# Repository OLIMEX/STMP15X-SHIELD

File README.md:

# STMP15X-SHIELD
Shield for Industrial grade Linux Computer STMP157-OLinuXino which adds two UEXT, 40 GPIO, micro SD card

Product page: https://www.olimex.com/Products/OLinuXino/STMP1/STMP15X-SHIELD/open-source-hardware

## License
* Hardware is released under CERN Open Hardware Licence Version 2 - Strongly Reciprocal https://spdx.org/licenses/CERN-OHL-S-2.0.html
* Software is released under GPL3 License
* Documentation is released under CC BY-SA 3.0 https://creativecommons.org/licenses/by-sa/3.0/

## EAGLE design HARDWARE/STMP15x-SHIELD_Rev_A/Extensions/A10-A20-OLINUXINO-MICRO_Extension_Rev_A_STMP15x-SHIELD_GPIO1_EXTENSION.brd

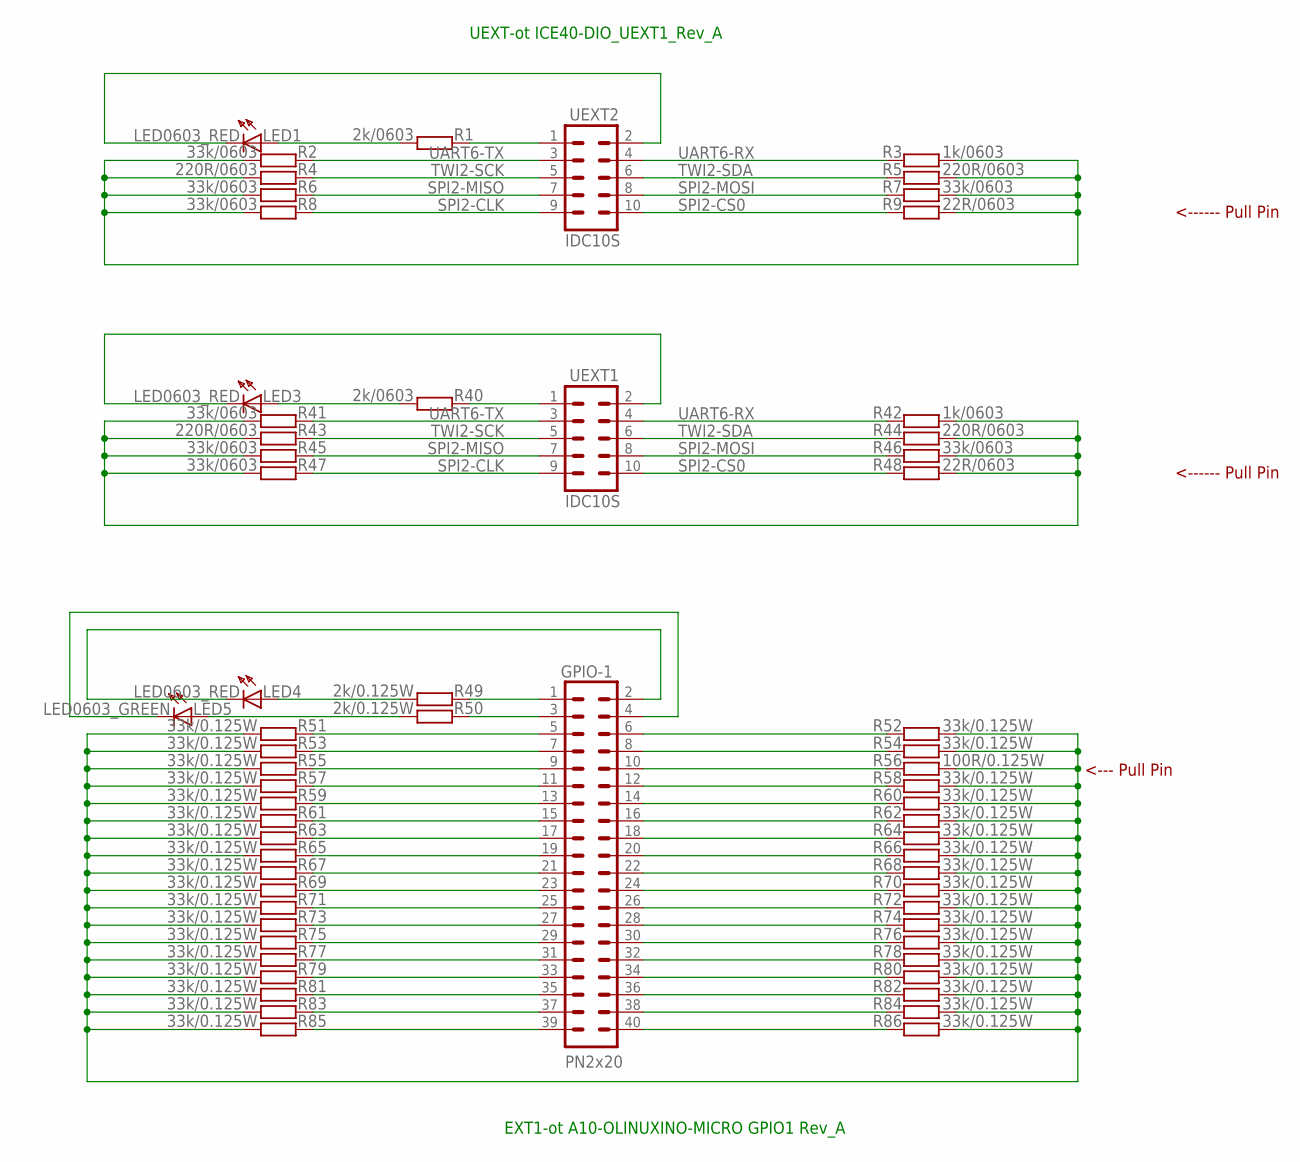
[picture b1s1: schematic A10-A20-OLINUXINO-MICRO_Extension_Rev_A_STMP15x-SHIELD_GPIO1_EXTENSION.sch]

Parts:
GPIO-1: PN2x20; ML40-FEMALE(PN2X20)
LED1, LED3, LED4: LED0603_RED; LED-0603
LED5: LED0603_GREEN; LED-0603
R1, R40: 2k/0603; 0204/5
R2, R6, R7, R8, R41, R45, R46, R47: 33k/0603; 0204/5
R3, R42: 1k/0603; 0204/5
R4, R5, R43, R44: 220R/0603; 0204/5
R9, R48: 22R/0603; 0204/5
R49, R50: 2k/0.125W; 0204/5
R51, R52, R53, R54, R55, R57, R58, R59, R60, R61, R62, R63, R64, R65, R66, R67, R68, R69, R70, R71, R72, R73, R74, R75, R76, R77, R78, R79, R80, R81, R82, R83, R84, R85, R86: 33k/0.125W; 0204/5
R56: 100R/0.125W; 0204/5
UEXT1, UEXT2: IDC10S; ML10-FEMALE(IDC10S/PCB)

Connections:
GPIO1: GPIO-1.35, R81.2
GPIO2: GPIO-1.37, R83.2
GPIO3: GPIO-1.39, R85.2
unnamed: LED1.A, R1.1
unnamed: R2.1, R3.1, R4.1, R5.1, R6.1, R7.1, R8.1, R9.1
unnamed: R51.1, R52.1, R53.1, R54.1, R55.1, R56.1, R57.1, R58.1, R59.1, R60.1, R61.1, R62.1, R63.1, R64.1, R65.1, R66.1, R67.1, R68.1, R69.1, R70.1, R71.1, R72.1, R73.1, R74.1, R75.1, R76.1, R77.1, R78.1, R79.1, R80.1, R81.1, R82.1, R83.1, R84.1, R85.1, R86.1
unnamed: R41.1, R42.1, R43.1, R44.1, R45.1, R46.1, R47.1, R48.1
unnamed: LED3.A, R40.1
unnamed: R1.2, UEXT2.1
unnamed: LED1.C, UEXT2.2
unnamed: LED5.A, R50.1
unnamed: LED4.A, R49.1
unnamed: LED3.C, UEXT1.2
unnamed: R40.2, UEXT1.1
unnamed: GPIO-1.3, R50.2
unnamed: GPIO-1.2, LED4.C
unnamed: GPIO-1.4, LED5.C
unnamed: GPIO-1.1, R49.2
NMI_N: GPIO-1.38, R84.2
PC3/NCE1: GPIO-1.21, R67.2
PC7/NRB1: GPIO-1.23, R69.2
PC16: GPIO-1.25, R71.2
PC17: GPIO-1.27, R73.2
PC18: GPIO-1.29, R75.2
PC23: GPIO-1.31, R77.2
PC24/NQS: GPIO-1.33, R79.2
PE0: GPIO-1.6, R52.2
PE1: GPIO-1.8, R54.2
PE2: GPIO-1.10, R56.2
PE3: GPIO-1.12, R58.2
PE4: GPIO-1.14, R60.2
PE5: GPIO-1.16, R62.2
PE6: GPIO-1.18, R64.2
PE7: GPIO-1.20, R66.2
PE8: GPIO-1.22, R68.2
PE9: GPIO-1.24, R70.2
PE10: GPIO-1.26, R72.2
PE11: GPIO-1.28, R74.2
PI0: GPIO-1.9, R55.2
PI1: GPIO-1.11, R57.2
PI2: GPIO-1.13, R59.2
PI3: GPIO-1.15, R61.2
PI10: GPIO-1.17, R63.2
PI11: GPIO-1.19, R65.2
PI14: GPIO-1.30, R76.2
PI15: GPIO-1.32, R78.2
RESET_N: GPIO-1.40, R86.2
SPI2-CLK: R8.2, R47.2, UEXT1.9, UEXT2.9
SPI2-CS0: R9.2, R48.2, UEXT1.10, UEXT2.10
SPI2-MISO: R6.2, R45.2, UEXT1.7, UEXT2.7
SPI2-MOSI: R7.2, R46.2, UEXT1.8, UEXT2.8
TWI0-SCK: GPIO-1.5, R51.2
TWI0-SDA: GPIO-1.7, R53.2
TWI2-SCK: R4.2, R43.2, UEXT1.5, UEXT2.5
TWI2-SDA: R5.2, R44.2, UEXT1.6, UEXT2.6
UART0-RX: GPIO-1.34, R80.2
UART0-TX: GPIO-1.36, R82.2
UART6-RX: R3.2, R42.2, UEXT1.4, UEXT2.4
UART6-TX: R2.2, R41.2, UEXT1.3, UEXT2.3

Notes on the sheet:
<--- Pull Pin
<------ Pull Pin
UEXT-ot ICE40-DIO_UEXT1_Rev_A
EXT1-ot A10-OLINUXINO-MICRO GPIO1 Rev_A

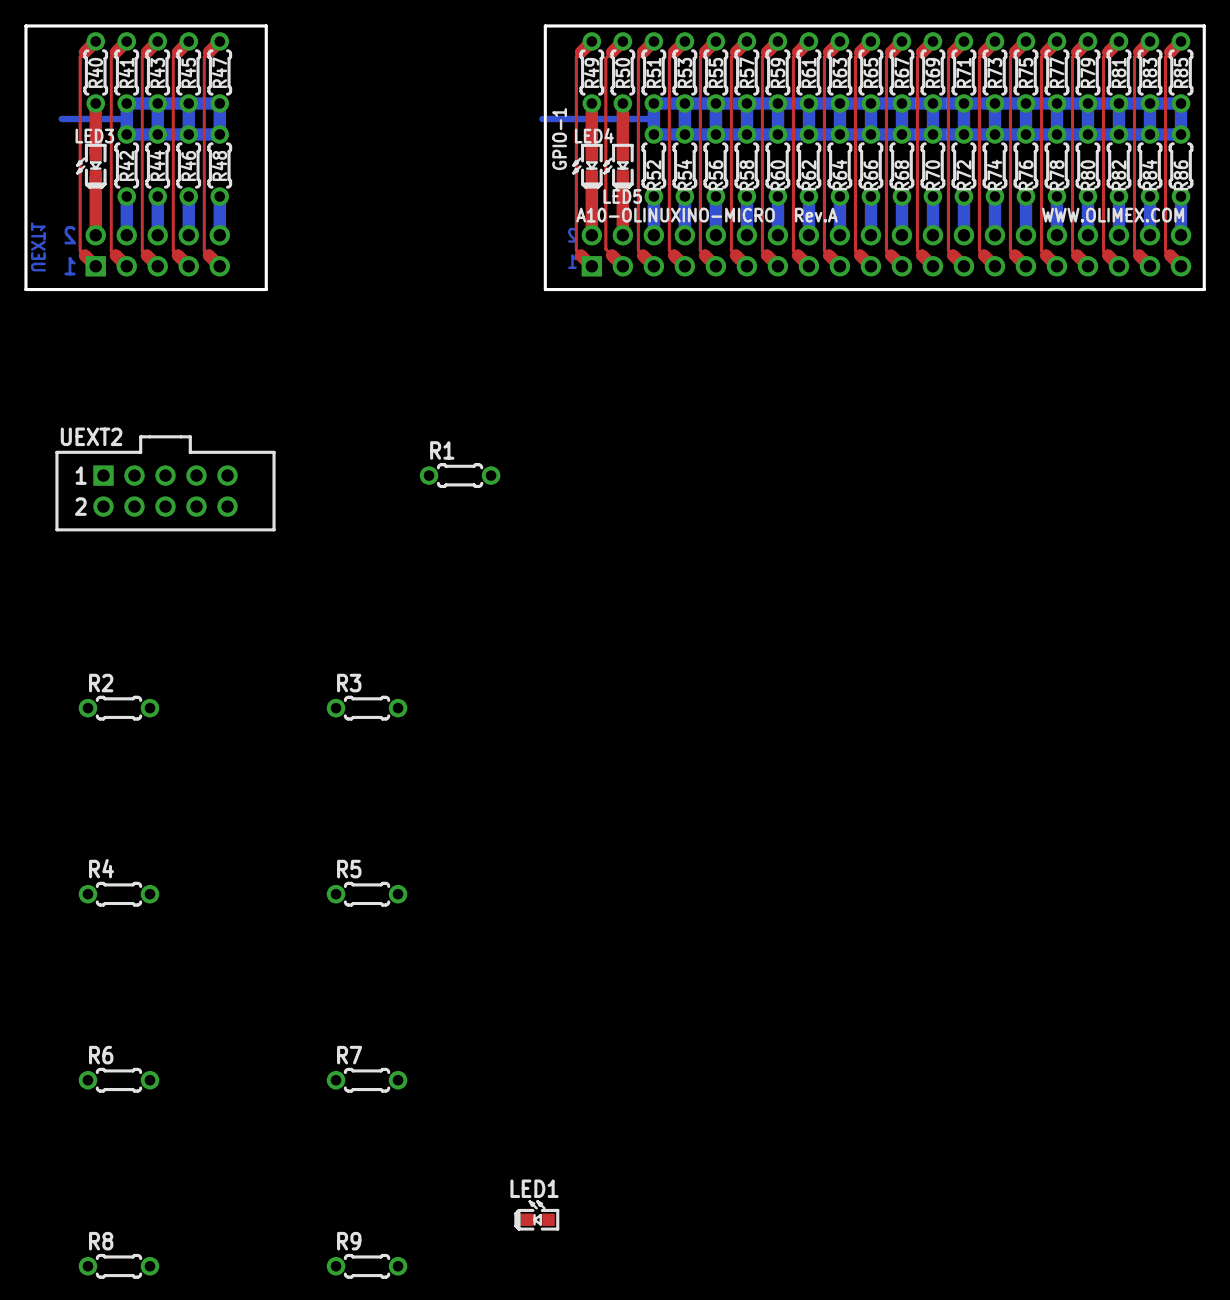
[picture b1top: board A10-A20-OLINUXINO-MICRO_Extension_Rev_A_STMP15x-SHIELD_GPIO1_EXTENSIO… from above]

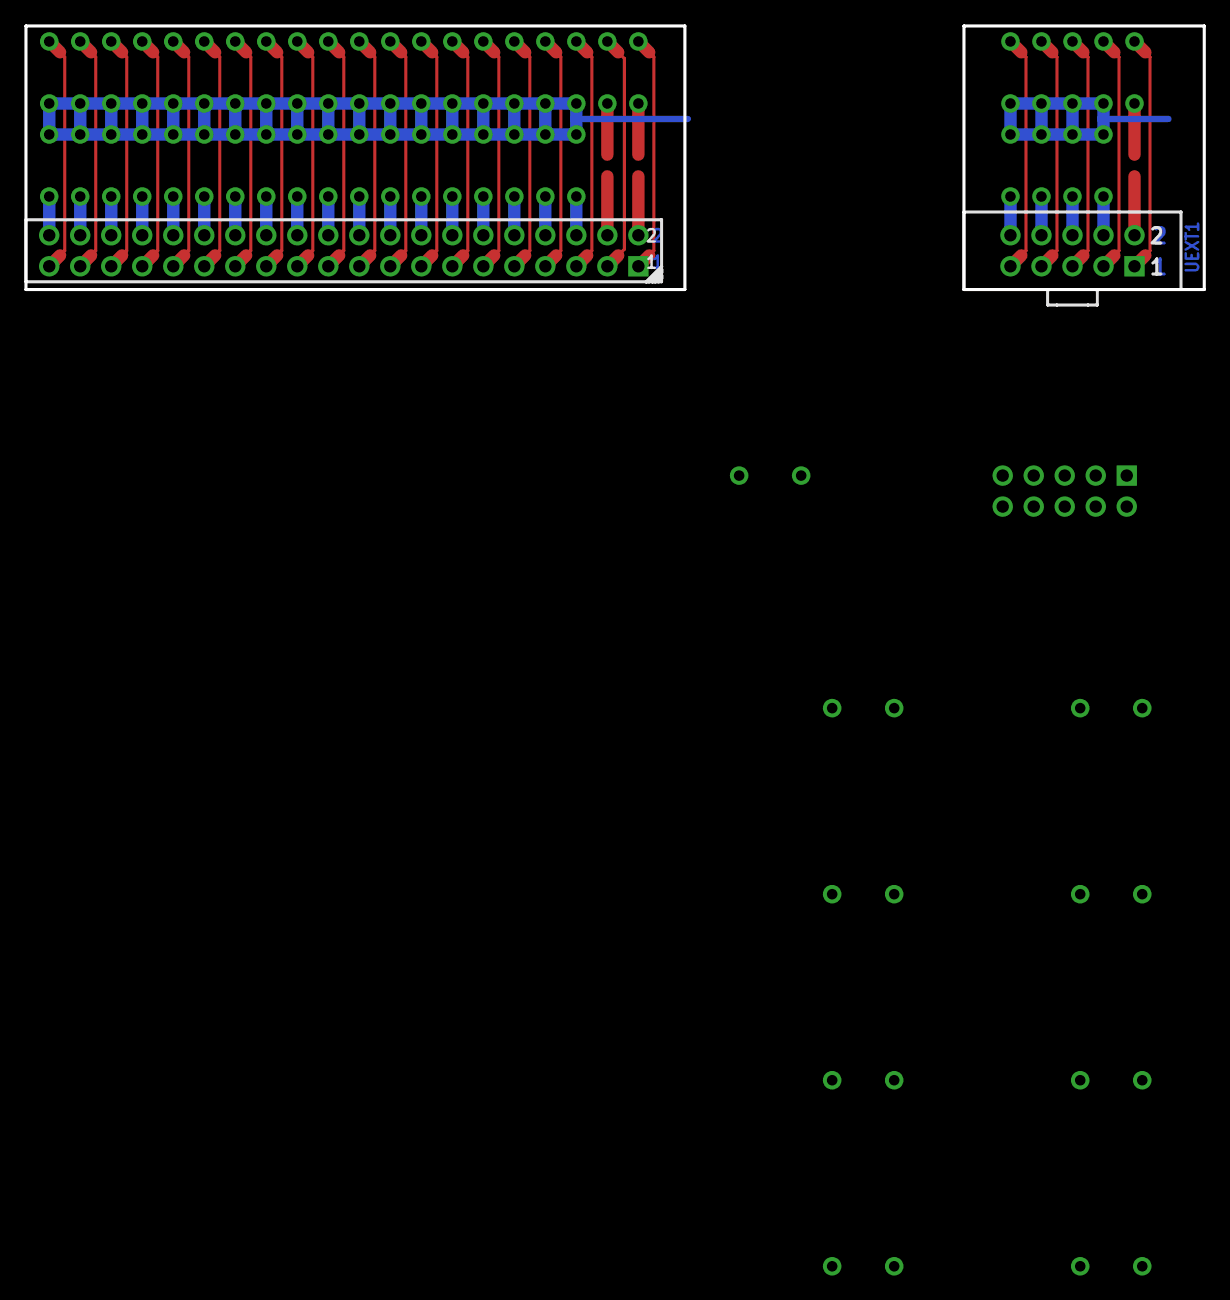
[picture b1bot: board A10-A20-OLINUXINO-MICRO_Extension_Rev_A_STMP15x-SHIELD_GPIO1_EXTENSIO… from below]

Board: 4 copper layers, 96.5 x 21.6 mm, 63 parts (2 on the bottom side), 59 nets.

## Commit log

2022-10-10 initial upload
